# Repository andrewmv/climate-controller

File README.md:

# Home Assistant Climate Controller

A wifi-enabled replacement for line-level electric heat controller thermostats installed in standard single-gang US electrical junction boxes

## Enclosure

OpenSCAD sources and rendered STLs for 3D printing

## PCB

EagleCAD schematics, boards, and reqresuite libraries.

## Software

Control software for ESPHome.io

## Reference

Part datasheets and vendor libraries

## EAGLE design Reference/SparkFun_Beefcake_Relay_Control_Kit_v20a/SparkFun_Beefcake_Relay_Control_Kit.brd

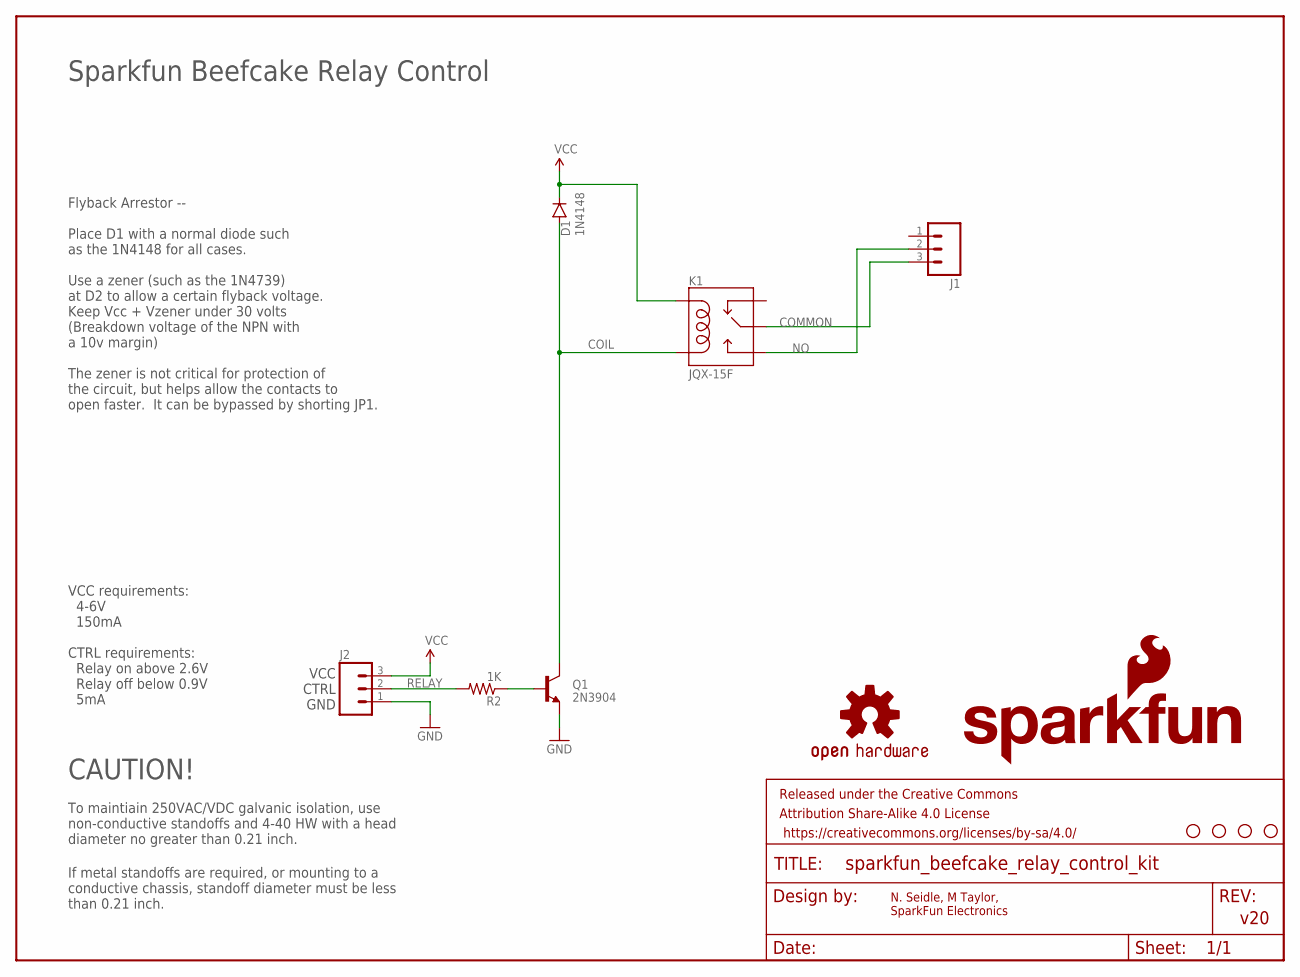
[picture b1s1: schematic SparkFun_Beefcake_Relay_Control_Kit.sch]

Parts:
D1: 1N4148; DIODE-1N4148-KIT
FRAME2: FRAME-LETTER; CREATIVE_COMMONS
J1: M03-SCREW-5MM; SCREWTERMINAL-5MM-3
J2: M03SCREW; SCREWTERMINAL-3.5MM-3
K1: JQX-15F; RELAY-T90
LOGO1: SFE_LOGO_NAME_FLAME.1_INCH; SFE_LOGO_NAME_FLAME_.1
Q1: 2N3904; TO-92-EZ
R2: 1K; AXIAL-0.3EZ
U$3, U$4, U$5, U$7: STAND-OFF
U$12: OSHW-LOGOS; OSHW-LOGO-S

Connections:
COIL: D1.A, K1.COIL2, Q1.3 (C)
COMMON: J1.3, K1.MAIN
GND: J2.1, Q1.1 (E)
unnamed: Q1.2 (B), R2.P$1 (1)
NO: J1.2, K1.NO
RELAY: J2.2, R2.P$2 (2)
VCC: D1.C, J2.3, K1.COIL1

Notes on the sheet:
N. Seidle, M Taylor, SparkFun Electronics
v20
Flyback Arrestor -- Place D1 with a normal diode such as the 1N4148 for all cases. Use a zener (such as the 1N4739) at D2 to allow a certain flyback voltage. Keep Vcc + Vzener under 30 volts (Breakdown voltage of the NPN with a 10v margin) The zener is not critical for protection of the circuit, bu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
To maintiain 250VAC/VDC galvanic isolation, use non-conductive standoffs and 4-40 HW with a head diameter no greater than 0.21 inch.
CAUTION!
If metal standoffs are required, or mounting to a conductive chassis, standoff diameter must be less than 0.21 inch.
VCC requirements: 4-6V 150mA CTRL requirements: Relay on above 2.6V Relay off below 0.9V 5mA
VCC CTRL GND
Sparkfun Beefcake Relay Control

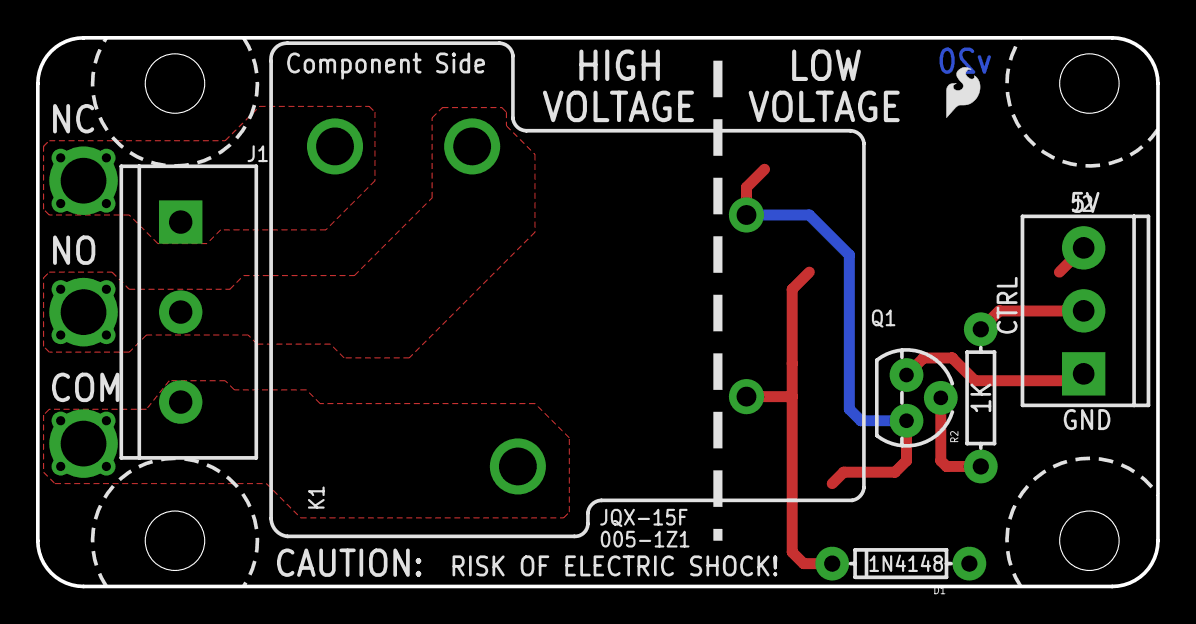
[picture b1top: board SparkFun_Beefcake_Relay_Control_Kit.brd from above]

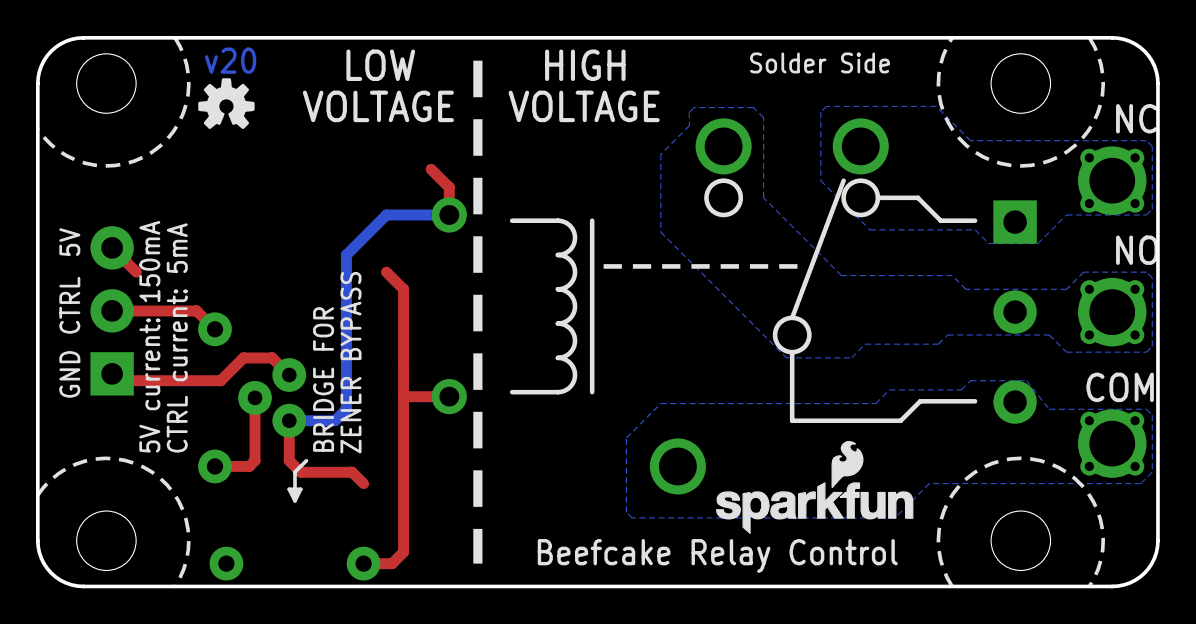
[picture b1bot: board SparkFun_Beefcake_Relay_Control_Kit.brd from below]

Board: 2 copper layers, 62.2 x 30.5 mm, 14 parts (2 on the bottom side), 7 nets.

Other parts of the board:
U$11: SFE-LOGO-FLAME

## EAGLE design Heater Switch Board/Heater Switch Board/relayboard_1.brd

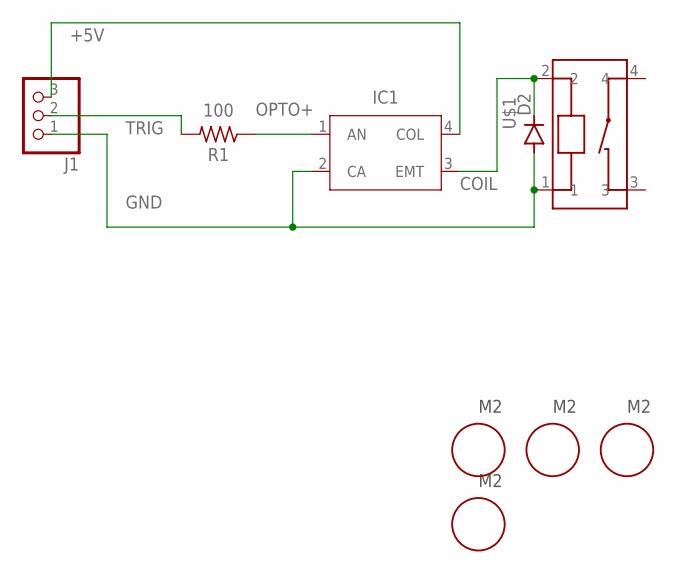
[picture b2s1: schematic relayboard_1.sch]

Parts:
D2: 1N4004; DO41-10
IC1: FOD817BSDSMT; DIP1016W60P279L460H460Q4B
J1: PINHD-1X3; 1X03
R1: 100; RESAD724W46L381D178B
S1: M2-POST
U$1: ALF1P05; LF_1_FORM_A_PCB
U$3, U$4, U$6: M2-POST

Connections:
+5V: IC1.4 (COL), J1.3
COIL: D2.C, IC1.3 (EMT), U$1.2
GND: D2.A, IC1.2 (CA), J1.1, U$1.1
OPTO+: IC1.1 (AN), R1.1
TRIG: J1.2, R1.2

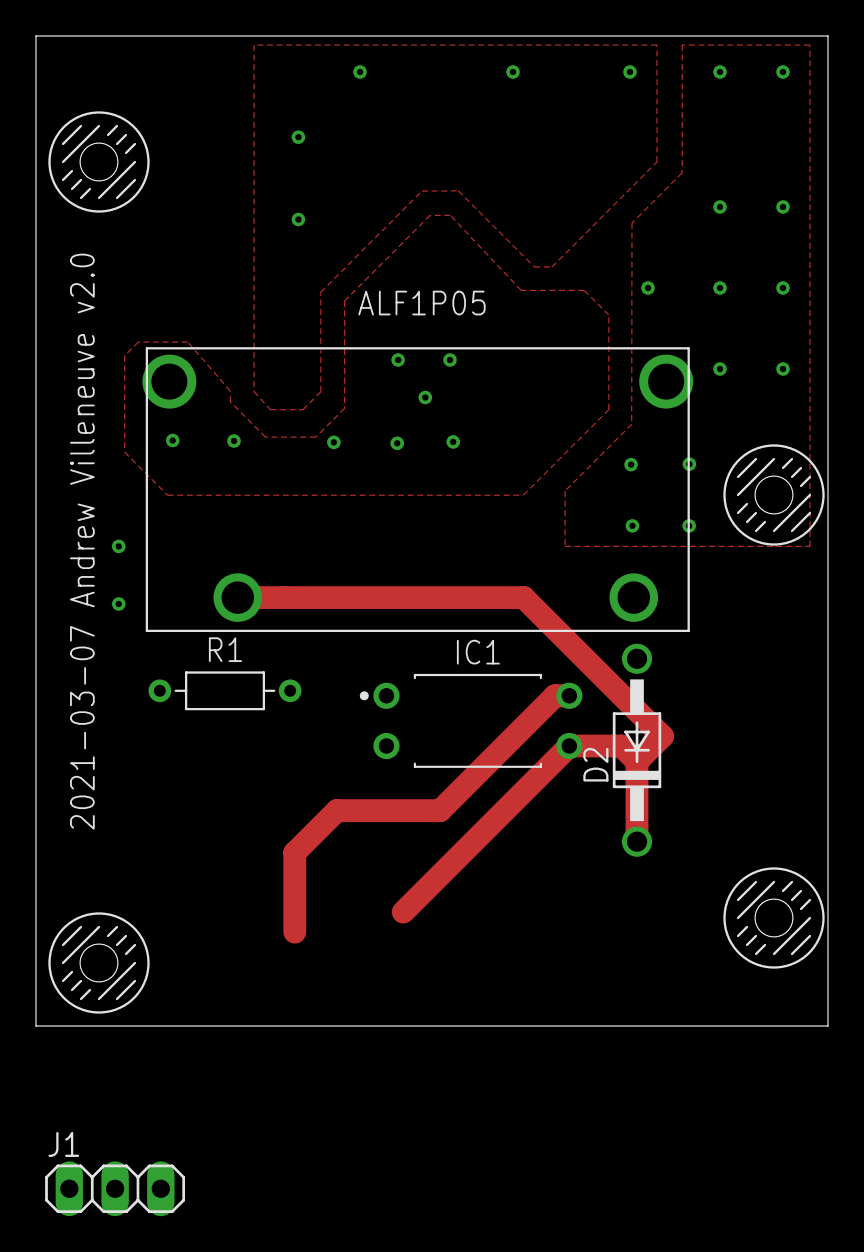
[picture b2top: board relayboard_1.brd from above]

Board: 2 copper layers, 44.0 x 55.0 mm, 9 parts (0 on the bottom side), 5 nets.

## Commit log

2021-05-18 gitignore
2021-05-26 PCB Pin Mapping
2021-05-26 Fixed pin mapping
2021-06-01 Checked in faceplate SCAD
2021-06-12 Changed some code
2021-06-12 Ignoring /dist
2021-06-12 Ignoring egg-info
2021-06-23 DHT sensor bracket
2021-06-23 Faceplate hooks
2021-06-23 Faceplate hook refactoring
2021-06-23 Face hook tabs
2021-06-24 DHT Slots
2021-06-24 STLs
2021-06-24 Label text, mesh fixes
2021-06-25 Faceplate bezel, support mesh
2021-06-26 Relay cover
2021-06-27 Global placeholder and support bools
2021-06-27 Minor fixes
2021-06-28 Relay sidewalls
2021-06-28 Relay connector openings
2021-06-28 Fixes
2021-06-29 Separated subprojects
2021-06-29 Added README
2021-07-02 Dial
2021-07-28 Reworked relay cover
2021-08-01 Enclosure v2.5
2021-08-01 Fixed relay cover screw head clearance, inset depth
2021-08-02 Misc fixes
2021-08-02 Reverting relay outline changes
2021-08-02 Fixed dial_stem_r, relay hole tolerances, simplified relay mount hole depth
2021-08-03 Changed faceplace threaded inserts from M3 to M2
2021-08-03 Max IC keepout
2021-08-03 Fixed DHT placement
2021-08-03 Added display well tolerance adjustment
2021-08-03 Hook slot bevels
2021-08-03 Moved face hook positions
2021-08-03 Added faceplace alignment adjustment
2021-08-04 Increased bezel depth to accommodate ESP backpack. Print set v2.7
2021-08-06 Fixed radius/diameter transposition on mounting stems
2021-08-06 Dial stem adjustment
2021-08-06 Dial project file
2021-08-08 Dial stem adjustments
2021-08-10 Cleanup, refactor, relay conn passthrough
2021-08-16 Relay cover AC taps
2021-08-16 Cleanup
2021-08-16 Relay front cover. v2.9 renders.
2021-08-17 Switched DHT mount from tab to PCB, resized for direct threading. v2.9 renders
2021-08-18 Added display timer feature
2021-08-18 Added software reset switch
2021-08-19 v2.9 render
2021-08-23 Explicitly defined sensor model
2021-08-28 Tweaks
2021-08-28 Added PSU Enclosure
2021-08-29 Fixed PSU Enclosure
2021-08-29 PSU Cover
2021-08-29 Room specific build
2021-08-29 Reference diagram
2021-08-29 Updated README with pics
2021-08-29 Fixed readme paths
2021-08-31 Added 5mm depth to faceplace
2021-09-03 Living room polynomial calibration
2021-09-03 Larger relay conn passthough, shallower relay bracket
2021-09-03 v3.1 Renders
2021-09-06 Added alphaden room
2021-09-06 Unflatten bracket, reposition relay passthrough, thicker jbox ears
2021-10-19 Updated Cura project
2021-10-19 Added rooms
2021-10-19 Added Bill of materials
2021-10-24 Updated gitignore
2021-10-24 More ignore juggling
2021-10-25 ESPHome 2021.8.0 Thermostat integration changes compatibility
2021-10-25 Added power failure persistence to settings
2021-10-25 Synced power failure persistence changes to all rooms
2021-12-13 Remove reboot switch
2021-12-13 Updated test thermostat for board v4.1F
2021-12-13 Moved / expanded comments
2021-12-13 Changed GPIO names and board type
2021-12-13 Added GPIO debug tool
2021-12-14 Migrated alphaden to 4.1F
2021-12-23 Added level shifter to PCB, updated GPIOs
2021-12-24 Power metering
2021-12-27 Added current metering sensors
2022-01-23 (Possibly) fixed race condition
2022-12-30 Disabled status LED
2023-01-27 Disabled relay control, onboarded api control
2023-09-30 Accommodated esphome code-breaking change
2023-09-30 Backported fix for boot-time display update race condition to target board v3.0 (NodeMCU)

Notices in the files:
parts and their libraries:
SparkFun-Aesthetics: Licensing: CC v3.0 Share-Alike You are welcome to use this library for commercial purposes.
SparkFun-Aesthetics: Released under the Creative Commons Attribution Share-Alike 4.0 License
SparkFun-Aesthetics: https://creativecommons.org/licenses/by-sa/4.0
